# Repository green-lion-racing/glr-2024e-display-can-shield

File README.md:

# CAN-Shield for STM32F469I-DISCO

STM32F469I-DISCO board compatible CAN shield.

### Overview

Provides 8V for the discovery board, from 12V car voltage.

Acts as can transciever for the discovery board.

Accessible screw terminals for buttons signals to the discovery board.

Can be directly slotted on to the board.

### Used parts

| Article                          | Description                 | Link                                                                                                          | Quantity |
| -------------------------------- | --------------------------- | ------------------------------------------------------------------------------------------------------------- | -------- |
| STMircoelectronics L9615D013TR   | 12V can transiever          | https://www.mouser.de/ProductDetail/STMicroelectronics/L9615D013TR?qs=RNlBCa%2FBPH2bRRygw50SdQ%3D%3D          | 1        |
| STMicroelectronics LF80CDT-TR    | voltage regulator 12V -> 8V | https://www.mouser.de/ProductDetail/STMicroelectronics/LF80CDT-TR?qs=jjdktuRV%2FggWfgmU%252Bn%252BoRA%3D%3D   | 1        |
| STMicroelectronics ESDCAN01-2BLY | dual-line TVS diode         | https://www.mouser.de/ProductDetail/STMicroelectronics/ESDCAN01-2BLY?qs=Ok1pvOkw6%2FpNzC2RQnWwPA%3D%3D        | 1        |
| Samsung CL10B104KB8NNNC          | capacitor 100nF             | https://www.mouser.de/ProductDetail/Samsung-Electro-Mechanics/CL10B104KB8NNNC?qs=349EhDEZ59rvGc2rLwVOdA%3D%3D | 2        |
| Vishay CRCW060368R1FKEA          | resistor 68ohm              | https://www.mouser.de/ProductDetail/Vishay-Dale/CRCW060368R1FKEA?qs=6z8JnUK2jyMngsBXu5il1A%3D%3D              | 1        |
| WECO 950-FB-04                   | 4-pin screw terminal        | https://www.buerklin.com/de/p/weco/leiterplattenklemmen/20877004/08H410/                                      | 1        |
| WECO 950-FB-08                   | 8-pin screw terminal        | https://www.buerklin.com/de/p/weco/leiterplattenklemmen/20877008/08H420/                                      | 1        |
| Generic header                   | 8-pin header 2.54mm         |                                                                                                               | 1        |
| Generic header                   | 6-pin header 2.54mm         |                                                                                                               | 1        |
| Generic socket                   | 2x8-pin socket 2.54mm       |                                                                                                               | 1        |

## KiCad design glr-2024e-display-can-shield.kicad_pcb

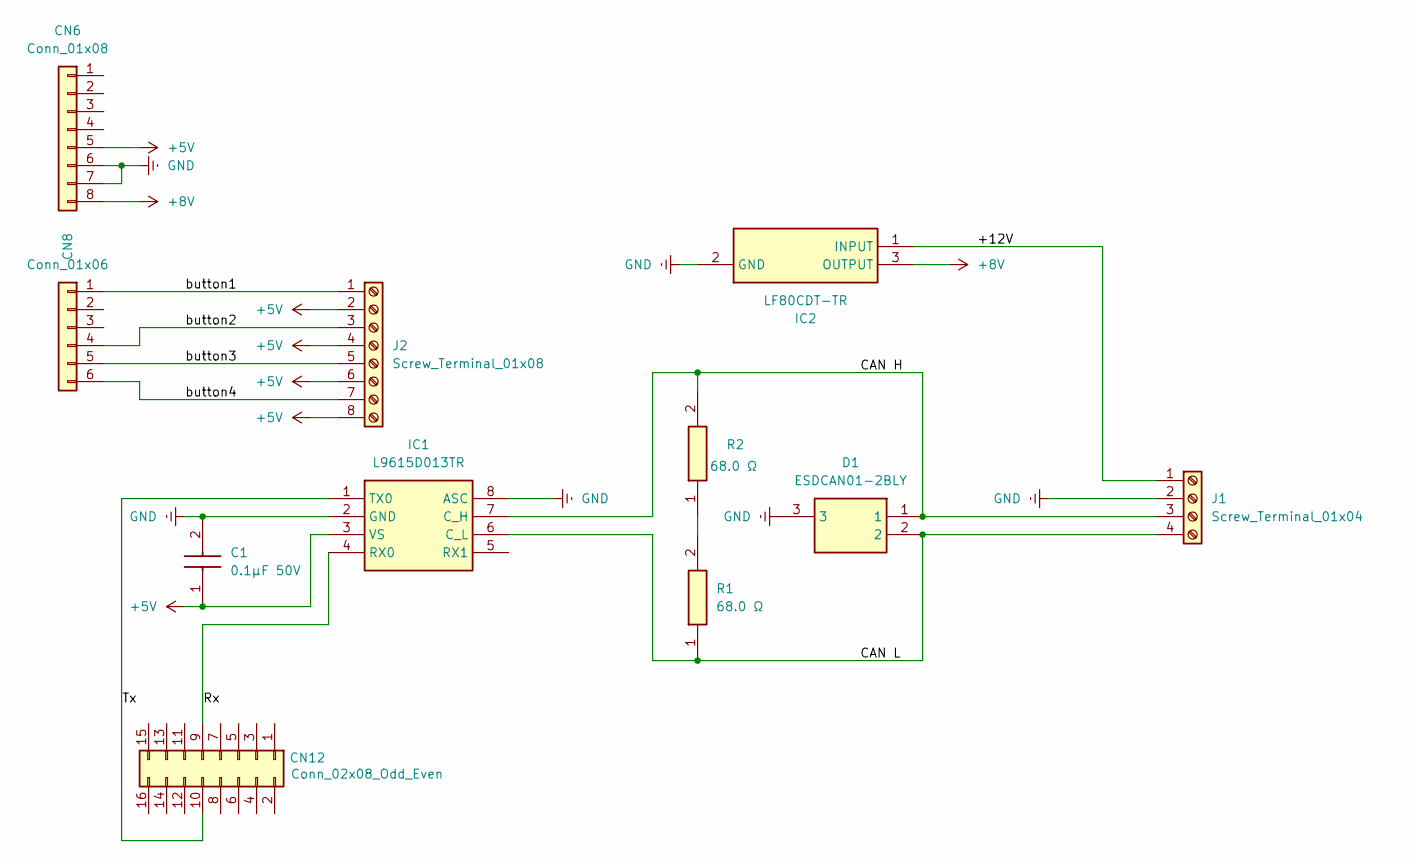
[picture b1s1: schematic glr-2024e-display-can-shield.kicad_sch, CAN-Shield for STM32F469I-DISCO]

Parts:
C1: 0.1μF 50V; CAPC1608X90N; Manufacturer_Part_Number CL10B104KB8NNNC
CN6: Conn_01x08; PinHeader_1x08_P2.54mm_Vertical
CN8: Conn_01x06; PinHeader_1x06_P2.54mm_Vertical
CN12: Conn_02x08_Odd_Even; PinSocket_2x08_P2.54mm_Vertical
D1: ESDCAN01-2BLY; SOT95P255X125-3N; Mouser Part Number 511-ESDCAN01-2BLY
IC1: L9615D013TR; SOIC127P600X175-8N; Manufacturer_Part_Number L9615D013TR; Mouser Part Number 511-L9615D-TR
IC2: LF80CDT-TR; LF80CDTTR; Mouser Part Number 511-LF80CDT-TR
J1: Screw_Terminal_01x04; WECO-950-FB-04
J2: Screw_Terminal_01x08; WECO-950-FB-08
R1, R2: 68.0 Ω; RESC1608X50N; Manufacturer_Part_Number CRCW060368R1FKEA

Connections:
+5V: C1.1, CN6.5, IC1.3 (VS), J2.2, J2.4, J2.6, J2.8
+8V: CN6.8, IC2.3 (OUTPUT)
/+12V: IC2.1 (INPUT), J1.1
/CAN H: D1.1, IC1.7 (C_H), J1.3, R2.2
/CAN L: D1.2, IC1.6 (C_L), J1.4, R1.1
/Rx: CN12.9, IC1.4 (RX0)
/Tx: CN12.10, IC1.1 (TX0)
/button1: CN8.1, J2.1
/button2: CN8.4, J2.3
/button3: CN8.5, J2.5
/button4: CN8.6, J2.7
GND: C1.2, CN6.6, CN6.7, D1.3, IC1.2 (GND), IC1.8 (ASC), IC2.2 (GND), J1.2
unnamed: R1.2, R2.1

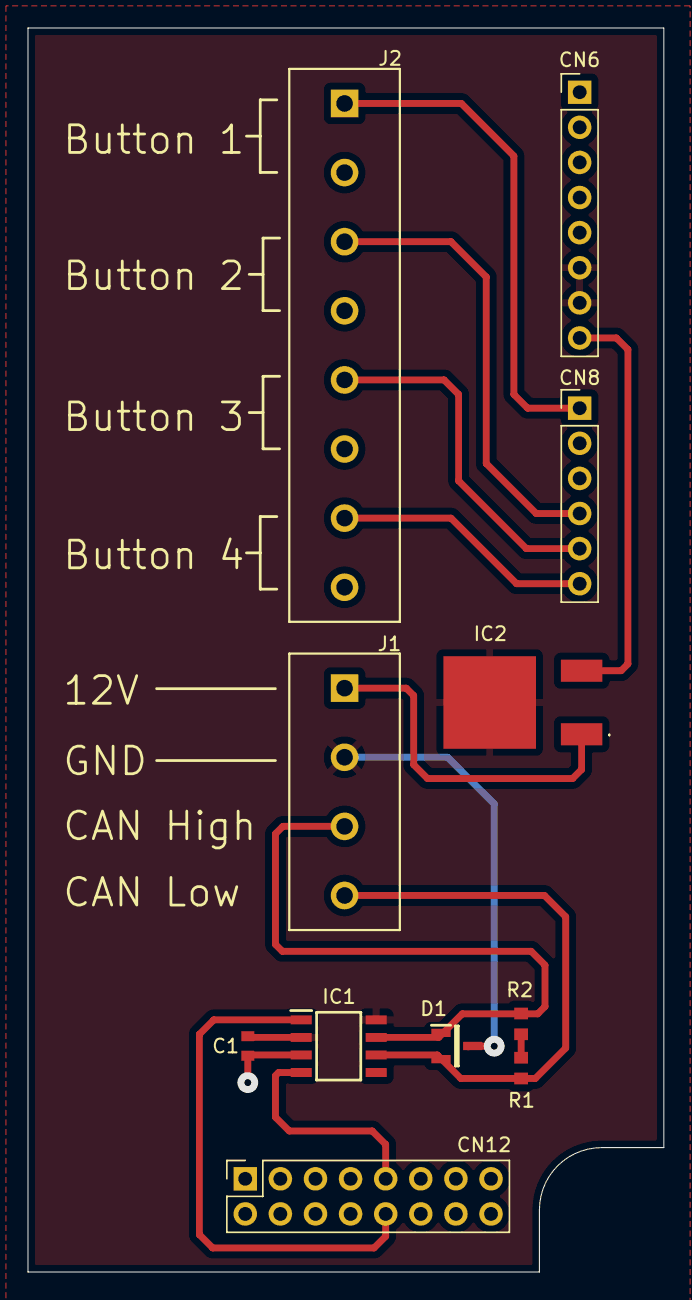
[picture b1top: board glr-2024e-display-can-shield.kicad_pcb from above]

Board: 2 copper layers, 46.0 x 90.0 mm, 11 parts (0 on the bottom side), 13 nets.

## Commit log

2025-01-27 switch to KiCad 8
2025-02-01 add initial pcb layout
2025-02-08 make 4pin and 8pin screw terminal instead of 12pin
    use exact footprint and 3d model
2025-02-15 add voltage regulator 12V -> 8V
    improve alignment of connectors
    add board outline
    add descriptions
2025-02-18 add board infos on pcb
    add two no GND zones
2025-03-01 explicitly define which parts to use
2025-03-08 fix capacitor connection
    fix silk on terminal
    add output folder
2025-03-08 move step export
2025-03-15 add overview of needed parts
    move schematic kicad 8 -> kicad 9
2025-04-23 apply footprint change for WECO-950-FB-04/WECO-950-FB-08
2025-06-25 use current date variable
2025-06-25 add output folder
    add *.pdf to ignore
